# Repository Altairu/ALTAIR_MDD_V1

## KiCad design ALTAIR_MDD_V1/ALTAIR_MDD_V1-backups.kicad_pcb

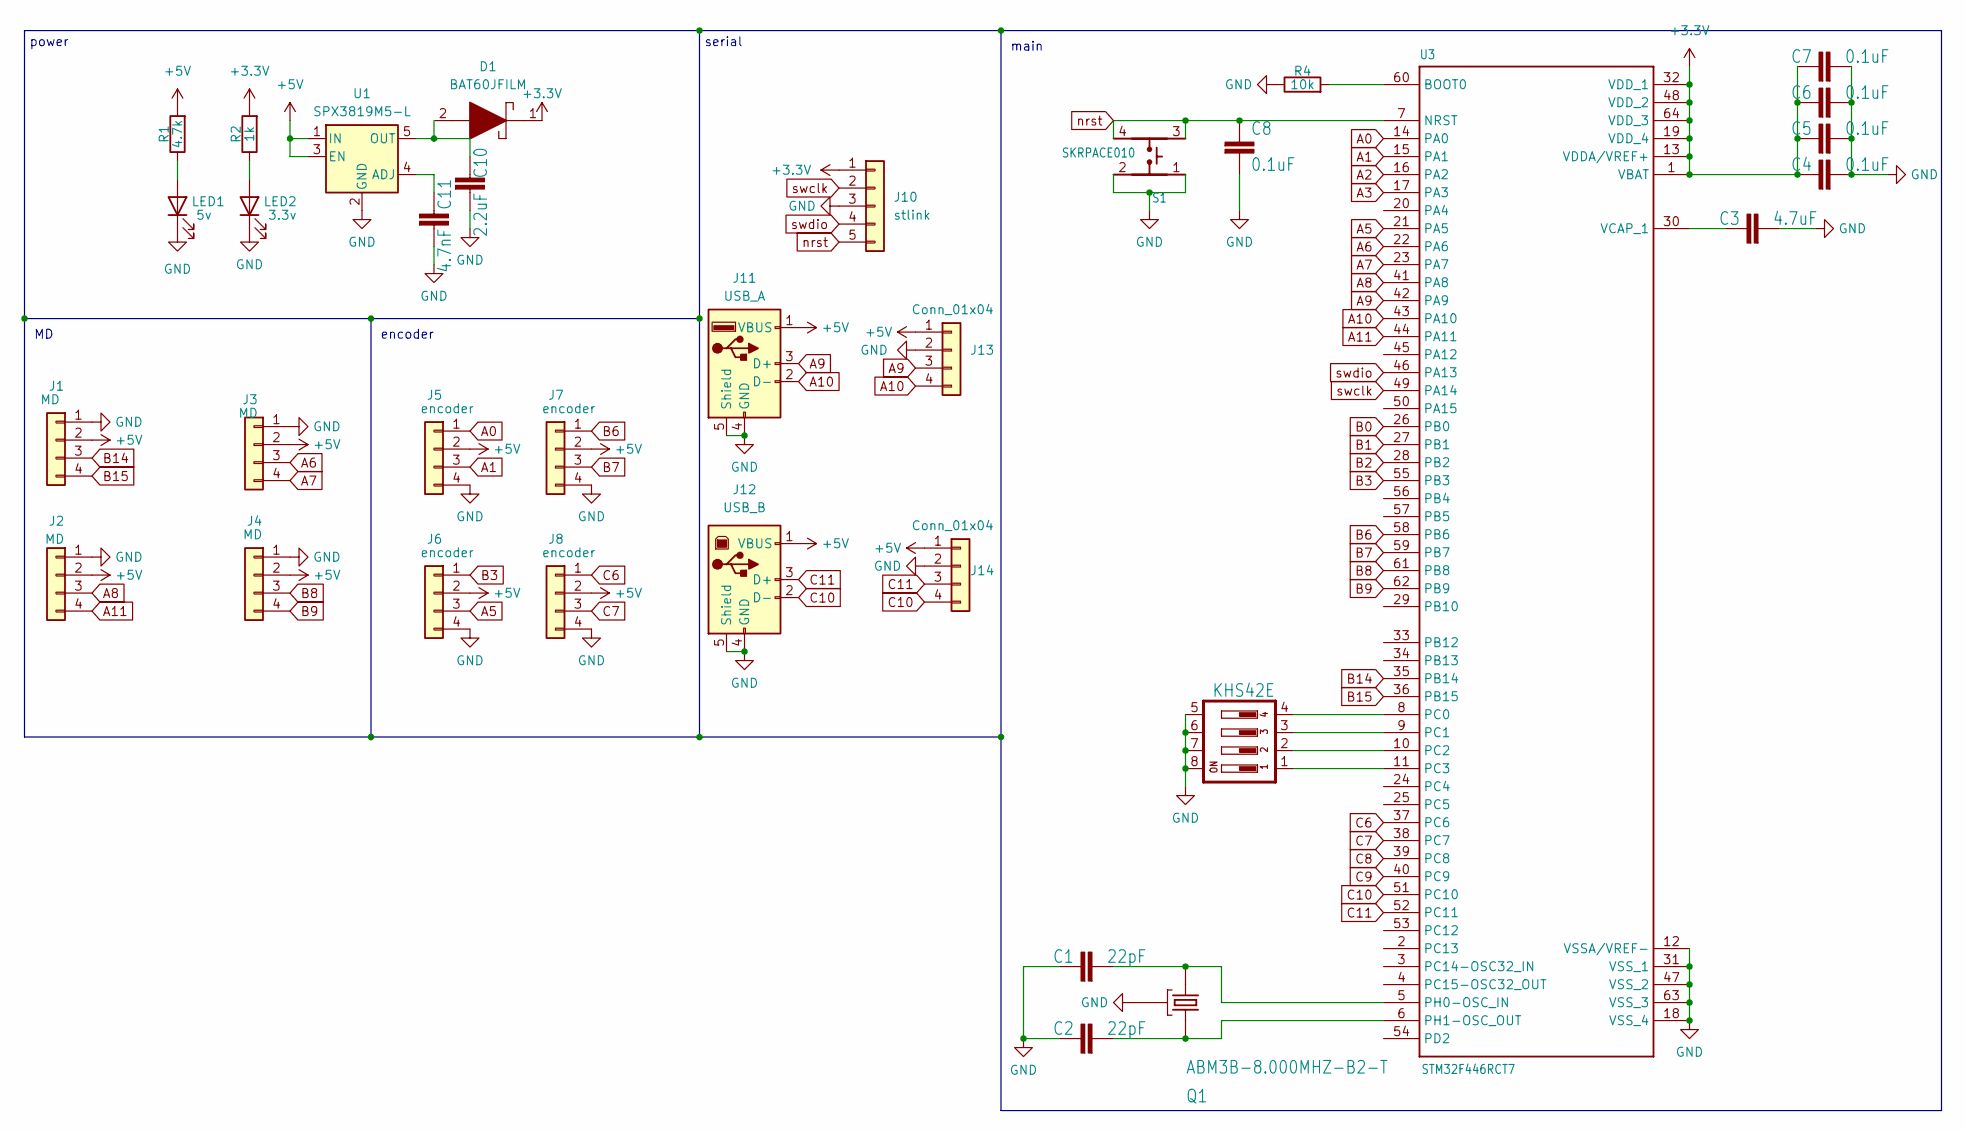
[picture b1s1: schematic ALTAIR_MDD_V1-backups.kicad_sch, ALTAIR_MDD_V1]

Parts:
C1, C2: 22pF; C_0603_1608Metric
C3: 4.7uF; C_0603_1608Metric
C4, C5, C6, C7, C8: 0.1uF; C_0603_1608Metric
C10: 2.2uF; C_0603_1608Metric
C11: 4.7nF; C_0603_1608Metric
D1: BAT60JFILM; SOD2513X117N; Manufacturer_Part_Number BAT60JFILM; Mouser Part Number 511-BAT60JFILM
J1, J2, J3, J4: MD; JST_XA_S04B-XASK-1_1x04_P2.50mm_Horizontal
J5, J6, J7, J8: encoder; JST_XA_S04B-XASK-1_1x04_P2.50mm_Horizontal
J10: stlink; JST_XA_S05B-XASK-1_1x05_P2.50mm_Horizontal
J11: USB_A; USB_A_Molex_67643_Horizontal
J12: USB_B; USB_B_Lumberg_2411_02_Horizontal
J13, J14: Conn_01x04; JST_XA_B04B-XASK-1_1x04_P2.50mm_Vertical
LED1: 5v; LED_0603_1608Metric
LED2: 3.3v; LED_0603_1608Metric
Q1: ABM3B-8.000MHZ-B2-T; Crystal_SMD_Abracon_ABM3B-4Pin_5.0x3.2mm
R1: 4.7k; R_0603_1608Metric
R2: 1k; R_0603_1608Metric
R4: 10k; R_0603_1608Metric
S1: SKRPACE010; SMT_4.2X3.2_
S2: KHS42E; SOIC127P600X175-8N
U1: SPX3819M5-L; SOT-23-5
U3: STM32F446RCT7; QFP50P1200X1200X160-64N

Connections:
+3.3V: C4.1, C5.1, C6.1, C7.1, D1.1, J10.1, R2.2, U3.1 (VBAT), U3.13 (VDDA/VREF+), U3.19 (VDD_4), U3.32 (VDD_1), U3.48 (VDD_2), U3.64 (VDD_3)
+5V: J1.2, J2.2, J3.2, J4.2, J5.2, J6.2, J7.2, J8.2, J11.1 (VBUS), J12.1 (VBUS), J13.1, J14.1, R1.2, U1.1 (IN), U1.3 (EN)
A0: J5.1, U3.14 (PA0)
A1: J5.3, U3.15 (PA1)
A2: U3.16 (PA2)
A3: U3.17 (PA3)
A5: J6.3, U3.21 (PA5)
A6: J3.3, U3.22 (PA6)
A7: J3.4, U3.23 (PA7)
A8: J2.3, U3.41 (PA8)
A9: J11.3 (D+), J13.3, U3.42 (PA9)
A10: J11.2 (D-), J13.4, U3.43 (PA10)
A11: J2.4, U3.44 (PA11)
B0: U3.26 (PB0)
B1: U3.27 (PB1)
B2: U3.28 (PB2)
B3: J6.1, U3.55 (PB3)
B6: J7.1, U3.58 (PB6)
B7: J7.3, U3.59 (PB7)
B8: J4.3, U3.61 (PB8)
B9: J4.4, U3.62 (PB9)
B14: J1.3, U3.35 (PB14)
B15: J1.4, U3.36 (PB15)
C6: J8.1, U3.37 (PC6)
C7: J8.3, U3.38 (PC7)
C8: U3.39 (PC8)
C9: U3.40 (PC9)
C10: J12.2 (D-), J14.4, U3.51 (PC10)
C11: J12.3 (D+), J14.3, U3.52 (PC11)
GND: C1.1, C2.1, C3.2, C4.2, C5.2, C6.2, C7.2, C8.2, C10.2, C11.2, J1.1, J2.1, J3.1, J4.1, J5.4, J6.4, J7.4, J8.4, J10.3, J11.4 (GND), J11.5 (Shield), J12.4 (GND), J12.5 (Shield), J13.2, J14.2, LED1.1 (K), LED2.1 (K), Q1.2 (GND), Q1.4 (GND), R4.1, S1.1, S1.2, S2.5, S2.6, S2.7, S2.8, U1.2 (GND), U3.12 (VSSA/VREF-), U3.18 (VSS_4), U3.31 (VSS_1), U3.47 (VSS_2), U3.63 (VSS_3)
unnamed: LED1.2 (A), R1.1
unnamed: LED2.2 (A), R2.1
unnamed: C11.1, U1.4 (ADJ)
unnamed: C10.1, D1.2, U1.5 (OUT)
unnamed: R4.2, U3.60 (BOOT0)
unnamed: S2.4, U3.8 (PC0)
unnamed: S2.3, U3.9 (PC1)
unnamed: S2.2, U3.10 (PC2)
unnamed: S2.1, U3.11 (PC3)
unnamed: C1.2, Q1.1, U3.5 (PH0-OSC_IN)
unnamed: C2.2, Q1.3, U3.6 (PH1-OSC_OUT)
unnamed: C3.1, U3.30 (VCAP_1)
nrst: C8.1, J10.5, S1.3, S1.4, U3.7 (NRST)
swclk: J10.2, U3.49 (PA14)
swdio: J10.4, U3.46 (PA13)

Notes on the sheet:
serial
encoder
main
power

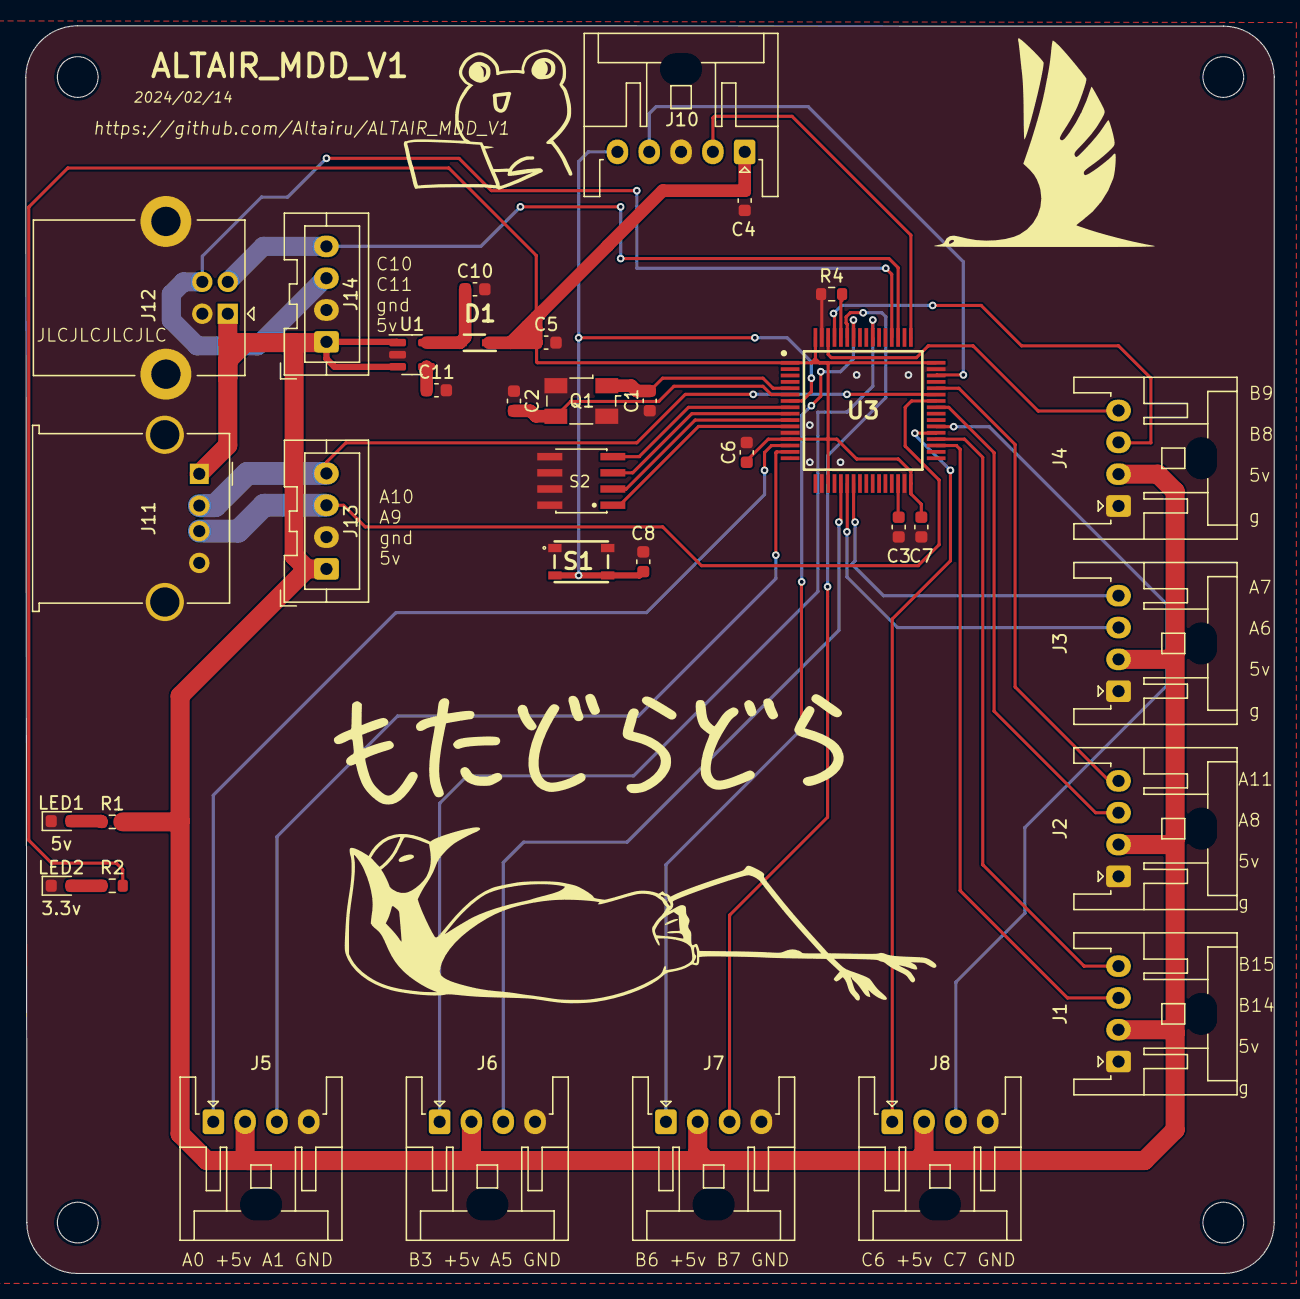
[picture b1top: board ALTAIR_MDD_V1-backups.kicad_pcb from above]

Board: 2 copper layers, 98.1 x 98.0 mm, 34 parts (0 on the bottom side), 38 nets.
